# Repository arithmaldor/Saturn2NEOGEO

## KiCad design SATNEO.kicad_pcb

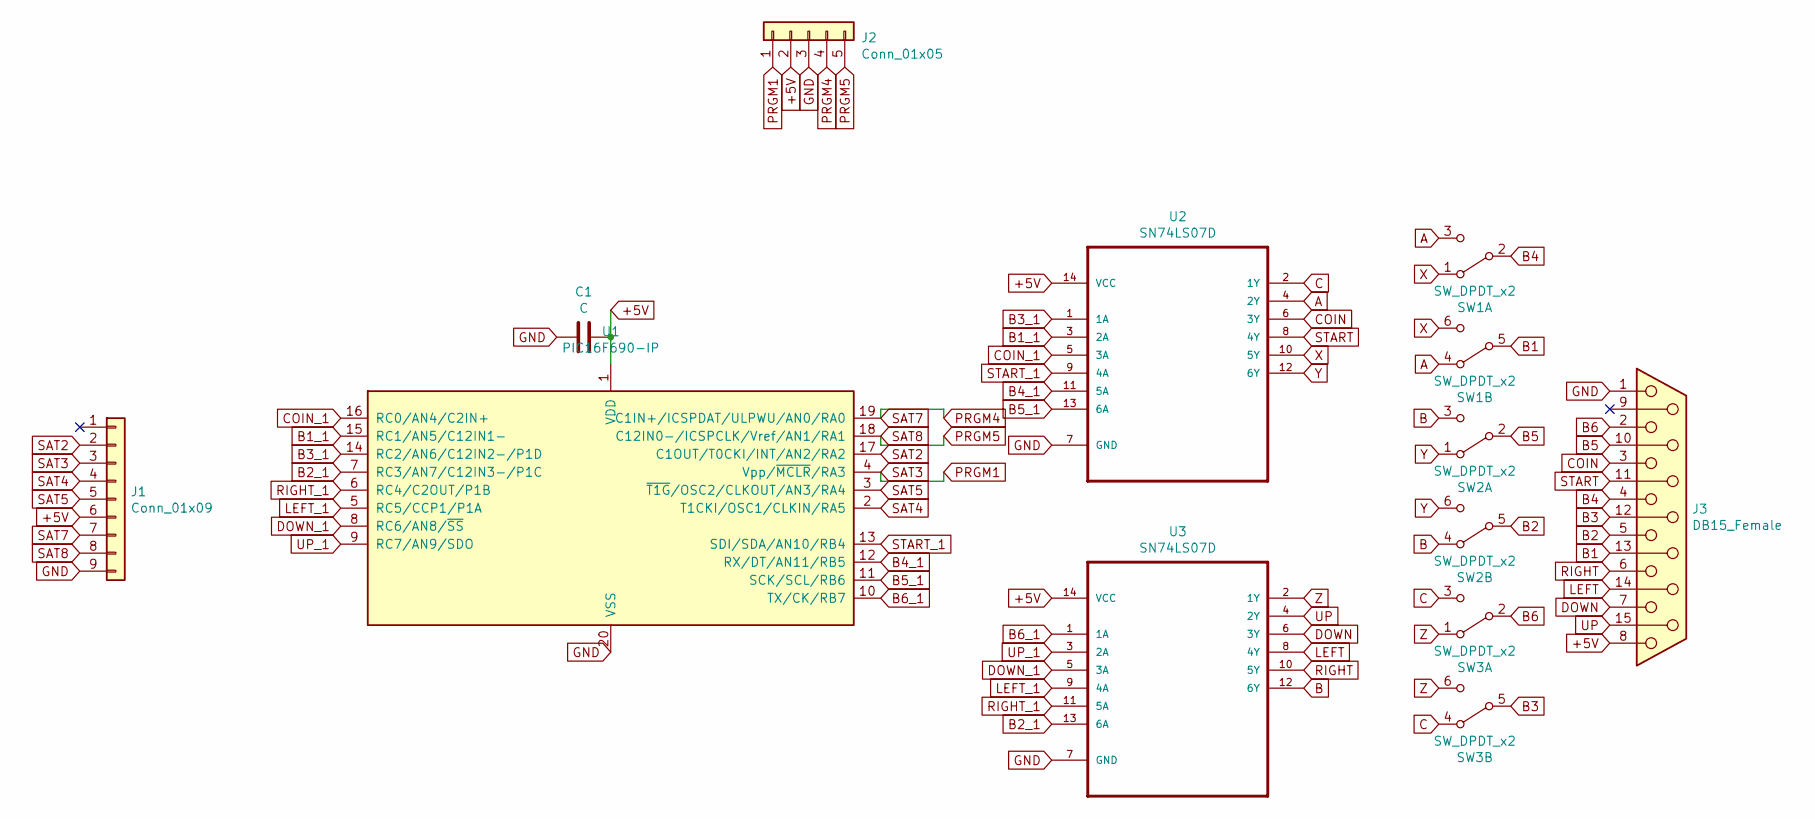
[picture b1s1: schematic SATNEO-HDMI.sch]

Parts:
C1: C; C_0603_1608Metric_Pad1.05x0.95mm_HandSolder
J1: Conn_01x09; SATURN_CONTROLLER_RA
J2: Conn_01x05; PinHeader_1x05_P2.54mm_Vertical
J3: DB15_Female; DSUB-15_Female_Horizontal_P2.77x2.84mm_EdgePinOffset7.70mm_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
SW1, SW2, SW3: SW_DPDT_x2; SW_CuK_JS202011CQN_DPDT_Straight
U1: PIC16F690-IP; SSOP-20_5.3x7.2mm_P0.65mm
U2, U3: SN74LS07D; SOIC-14_3.9x8.7mm_P1.27mm

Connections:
+5V: C1.1, J1.6, J2.2, J3.8, U1.1 (VDD), U2.14 (VCC), U3.14 (VCC)
A: SW1.3 (C), SW1.4 (A), U2.4 (2Y)
B: SW2.3 (C), SW2.4 (A), U3.12 (6Y)
B1: J3.13, SW1.5 (B)
B1_1: U1.15 (RC1/AN5/C12IN1-), U2.3 (2A)
B2: J3.5, SW2.5 (B)
B2_1: U1.7 (RC3/AN7/C12IN3-/P1C), U3.13 (6A)
B3: J3.12, SW3.5 (B)
B3_1: U1.14 (RC2/AN6/C12IN2-/P1D), U2.1 (1A)
B4: J3.4, SW1.2 (B)
B4_1: U1.12 (RX/DT/AN11/RB5), U2.11 (5A)
B5: J3.10, SW2.2 (B)
B5_1: U1.11 (SCK/SCL/RB6), U2.13 (6A)
B6: J3.2, SW3.2 (B)
B6_1: U1.10 (TX/CK/RB7), U3.1 (1A)
C: SW3.3 (C), SW3.4 (A), U2.2 (1Y)
COIN: J3.3, U2.6 (3Y)
COIN_1: U1.16 (RC0/AN4/C2IN+), U2.5 (3A)
DOWN: J3.7, U3.6 (3Y)
DOWN_1: U1.8 (RC6/AN8/~SS~), U3.5 (3A)
GND: C1.2, J1.9, J2.3, J3.1, U1.20 (VSS), U2.7 (GND), U3.7 (GND)
LEFT: J3.14, U3.8 (4Y)
LEFT_1: U1.5 (RC5/CCP1/P1A), U3.9 (4A)
PRGM1: J1.3, J2.1, U1.4 (Vpp/~MCLR~/RA3)
PRGM4: J1.7, J2.4, U1.19 (C1IN+/ICSPDAT/ULPWU/AN0/RA0)
PRGM5: J1.8, J2.5, U1.18 (C12IN0-/ICSPCLK/Vref/AN1/RA1)
RIGHT: J3.6, U3.10 (5Y)
RIGHT_1: U1.6 (RC4/C2OUT/P1B), U3.11 (5A)
SAT2: J1.2, U1.17 (C1OUT/T0CKI/INT/AN2/RA2)
SAT4: J1.4, U1.2 (T1CKI/OSC1/CLKIN/RA5)
SAT5: J1.5, U1.3 (~T1G~/OSC2/CLKOUT/AN3/RA4)
START: J3.11 (P111), U2.8 (4Y)
START_1: U1.13 (SDI/SDA/AN10/RB4), U2.9 (4A)
UP: J3.15, U3.4 (2Y)
UP_1: U1.9 (RC7/AN9/SDO), U3.3 (2A)
X: SW1.1 (A), SW1.6 (C), U2.10 (5Y)
Y: SW2.1 (A), SW2.6 (C), U2.12 (6Y)
Z: SW3.1 (A), SW3.6 (C), U3.2 (1Y)

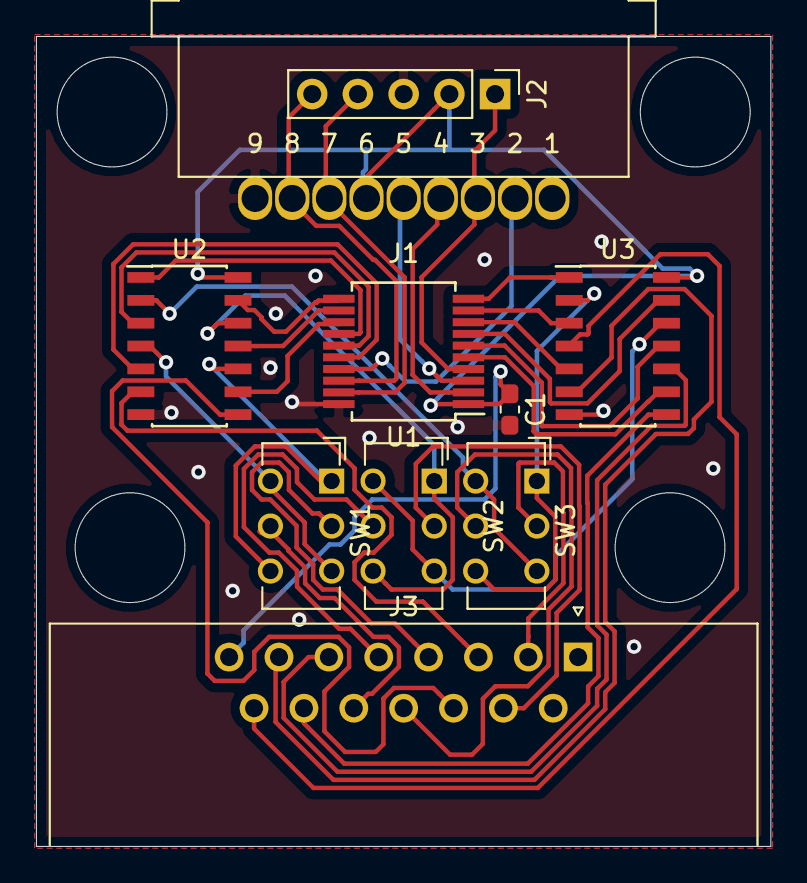
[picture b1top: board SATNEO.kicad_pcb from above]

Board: 2 copper layers, 40.8 x 45.0 mm, 14 parts (0 on the bottom side), 38 nets.

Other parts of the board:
 : MountingHole_3.2mm_M3
 #2,  #3,  #4: MountingHole_3.2mm_M3

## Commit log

2019-07-31 Began process of making version with HDMI in for blissbox cables instead of female saturn cables
